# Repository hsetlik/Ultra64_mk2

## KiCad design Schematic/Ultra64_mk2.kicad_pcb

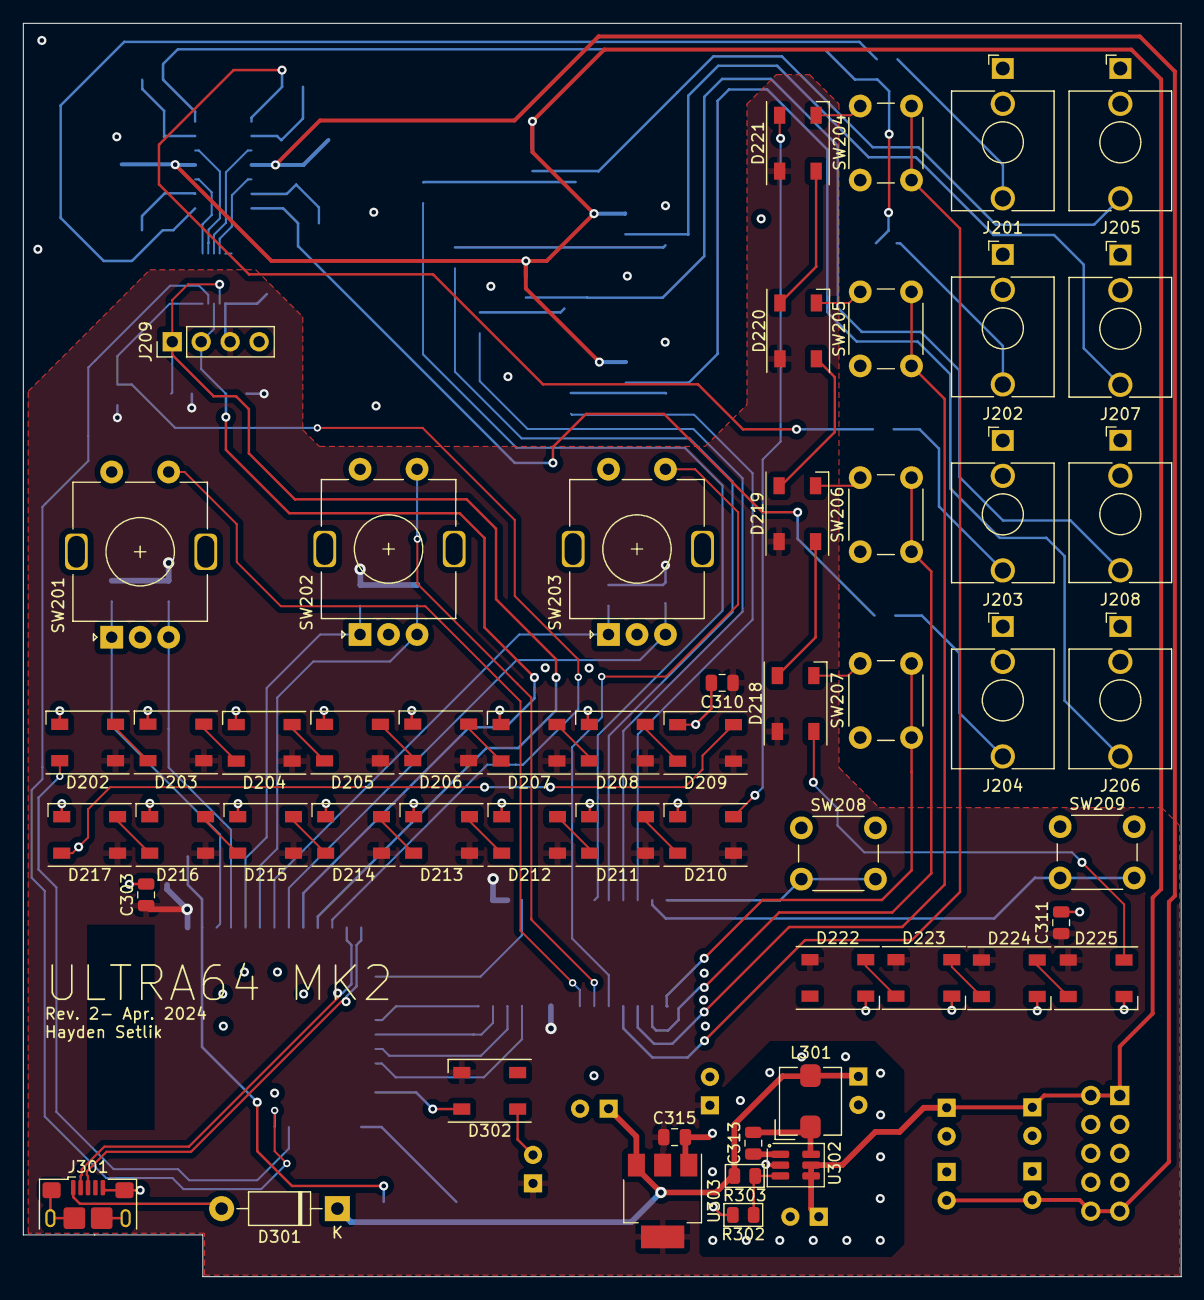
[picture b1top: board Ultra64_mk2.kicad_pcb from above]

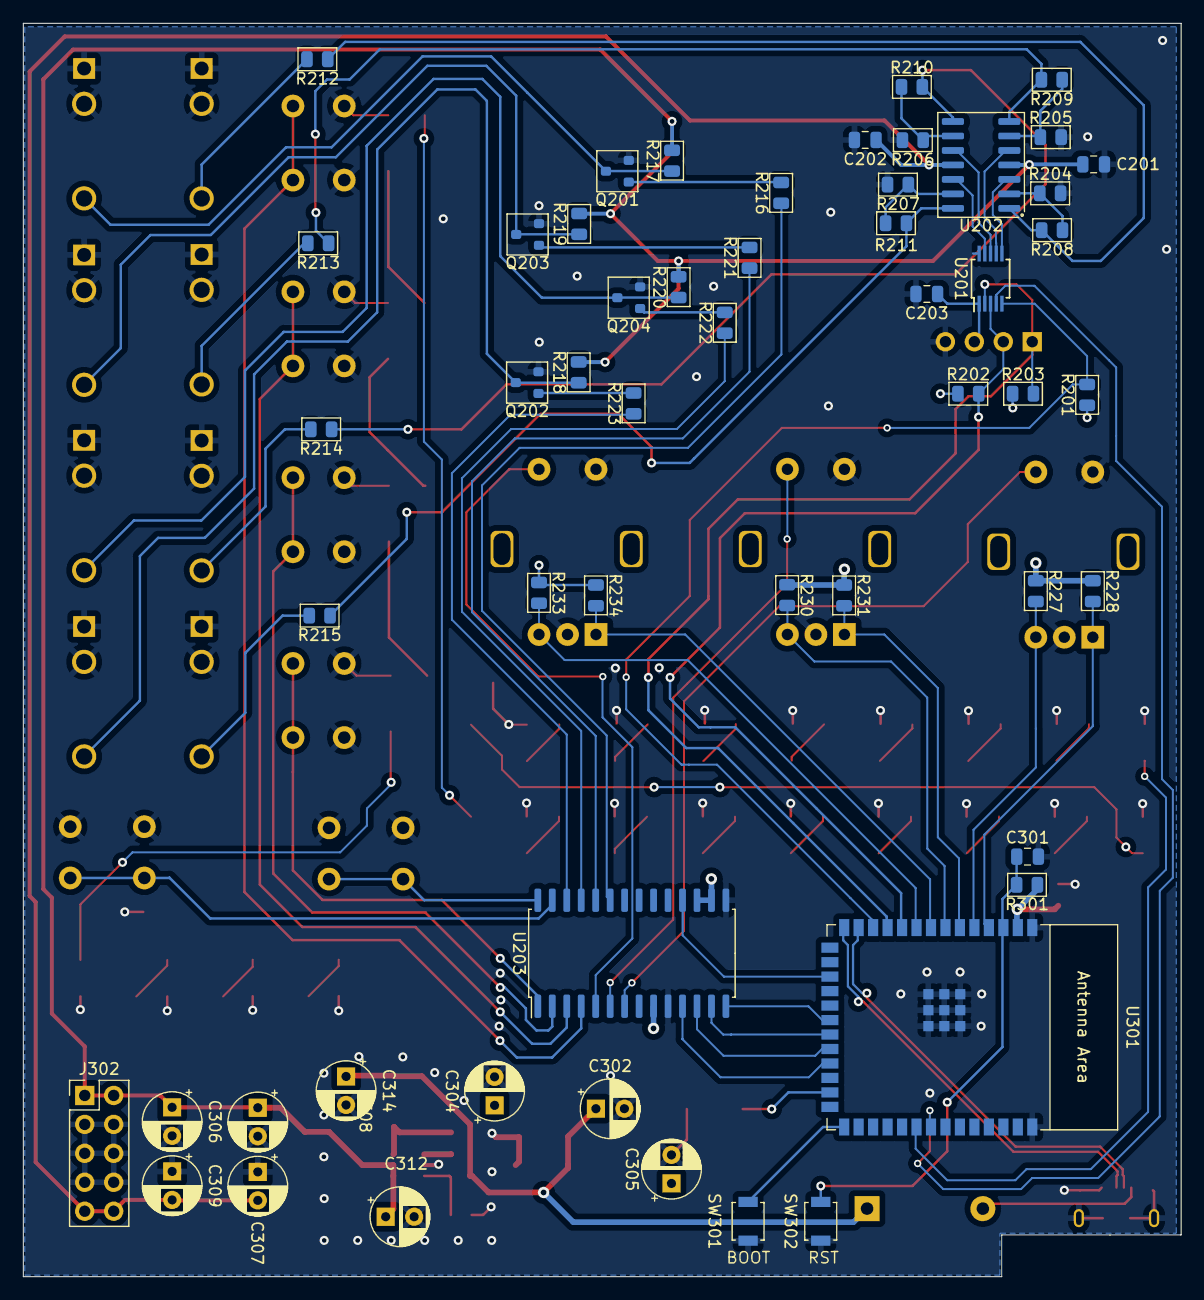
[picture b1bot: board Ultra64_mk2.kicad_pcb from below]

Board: 4 copper layers, 101.6 x 110.0 mm, 109 parts (54 on the bottom side), 90 nets.

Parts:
C201, C202, C203, C301, C303, C313: 0.1uF; C_0805_2012Metric
C302, C304, C305, C312, C314: 10uF; CP_Radial_D5.0mm_P2.50mm
C306, C307, C309: 22uF; CP_Radial_D5.0mm_P2.50mm
C308: 2.2uF; CP_Radial_D5.0mm_P2.50mm
C310: 2.2nF; C_0805_2012Metric
C311: 220nF; C_0805_2012Metric
C315: 2.2uF; C_0805_2012Metric
D202, D203, D204, D205, D206, D207, D208, D209, D210, D211, D212, D213, D214, D215, D216, D217, D218, D219, D220, D221, D222, D223, D224, D225: SK6812; LED_SK6812_PLCC4_5.0x5.0mm_P3.2mm
D301: 1N4002; D_DO-41_SOD81_P10.16mm_Horizontal
D302: WS2812B; LED_SK6812_PLCC4_5.0x5.0mm_P3.2mm
J201: CV1; Jack_3.5mm_QingPu_WQP-PJ398SM_Vertical_CircularHoles
J202: CV2; Jack_3.5mm_QingPu_WQP-PJ398SM_Vertical_CircularHoles
J203: CV3; Jack_3.5mm_QingPu_WQP-PJ398SM_Vertical_CircularHoles
J204: CV4; Jack_3.5mm_QingPu_WQP-PJ398SM_Vertical_CircularHoles
J205: GATE1; Jack_3.5mm_QingPu_WQP-PJ398SM_Vertical_CircularHoles
J206: GATE4; Jack_3.5mm_QingPu_WQP-PJ398SM_Vertical_CircularHoles
J207: GATE2; Jack_3.5mm_QingPu_WQP-PJ398SM_Vertical_CircularHoles
J208: GATE3; Jack_3.5mm_QingPu_WQP-PJ398SM_Vertical_CircularHoles
J209: Display; PinHeader_1x04_P2.54mm_Vertical
J301: USB_B_Micro; USB_Micro-B_Amphenol_10118193-0001LF_Horizontal
J302: Conn_02x05_Odd_Even; PinHeader_2x05_P2.54mm_Vertical
L301: 4.7uH; L_Bourns_SRP5030T
Q201, Q202, Q203, Q204: BC847; SOT-23
R201: 100k; R_0805_2012Metric
R202, R203: 2k2; R_0805_2012Metric
R204, R205, R206, R207: 47k; R_0805_2012Metric
R208, R209, R210, R211: 68k; R_0805_2012Metric
R212, R213, R214, R215: 220R; R_0805_2012Metric
R216, R221, R222, R223: 1k; R_0805_2012Metric
R217, R218, R219, R220, R227, R228, R230, R231, R233, R234, R301: 10k; R_0805_2012Metric
R302: 22k; R_0805_2012Metric
R303: 89k; R_0805_2012Metric
SW201, SW202, SW203: RotaryEncoder_Switch; RotaryEncoder_Alps_EC11E-Switch_Vertical_H20mm_5Pin
SW204, SW205, SW206, SW207, SW208, SW209: SW_SPST; SW_PUSH_6mm_H5mm
SW301, SW302: SW_SPST; SW_SPST_B3U-1000P
U201: MCP4728; MSOP-10_3x3mm_P0.5mm
U202: TL074; SOIC-14_3.9x8.7mm_P1.27mm
U203: MCP23S17_SO; SOIC-28W_7.5x17.9mm_P1.27mm
U301: ESP32-S3-WROOM-1
U302: LMR50410-Q; SOT-23-6_BigPads
U303: AMS1117; SOT-223-3_TabPin2

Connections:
+3.3V: C203.1, C303.1, C304.1, C305.1, C310.1, C311.1, C315.1, D202.3 (VDD), D203.3 (VDD), D204.3 (VDD), D205.3 (VDD), D206.3 (VDD), D207.3 (VDD), D208.3 (VDD), D209.3 (VDD), D210.3 (VDD), D211.3 (VDD), D212.3 (VDD), D213.3 (VDD), D214.3 (VDD), D215.3 (VDD), D216.3 (VDD), D217.3 (VDD), D218.3 (VDD), D219.3 (VDD), D220.3 (VDD), D221.3 (VDD), D222.3 (VDD), D223.3 (VDD), D224.3 (VDD), D225.3 (VDD), D302.1 (VDD), J209.3, R201.1, R202.1, R203.1, R227.1, R228.1, R230.1, R231.1, R233.1, R234.1, R301.1, U201.1 (VDD), U203.9 (VDD), U203.16 (A1), U203.17 (A2), U301.2 (3V3), U303.2 (VO)
+5V: C302.1, C314.1, D301.1 (K), L301.2, R303.2, U303.3 (VI)
+12V: C201.1, C306.1, C308.1, C312.1, J302.1, J302.2, R217.2, R218.2, R219.2, R220.2, U202.4 (V+), U302.4 (EN), U302.5 (VIN)
-12V: C202.1, C307.2, C309.2, J302.9, J302.10, U202.11 (V-)
C1: SW204.2 (B), U203.4 (GPB3)
C1_CV: J201.T, R212.2
C1_GATE: J205.T, Q201.3 (C), R217.1
C2: SW205.2 (B), U203.3 (GPB2)
C2_CV: J202.T, R213.2
C2_GATE: J207.T, Q203.3 (C), R219.1
C3: SW206.2 (B), U203.2 (GPB1)
C3_CV: J203.T, R214.2
C3_GATE: J208.T, Q204.3 (C), R220.1
C4: SW207.2 (B), U203.1 (GPB0)
C4_CV: J204.T, R215.2
C4_GATE: J206.T, Q202.3 (C), R218.1
DAC_RDY: R201.2, U201.5 (RDY/~BSY), U301.12 (GPIO8/TOUCH8/ADC1_CH7/SUBSPICS1)
EN: C301.1, R301.2, SW302.1 (A), U301.3 (EN)
ENCA_B: SW201.S1, U203.7 (GPB6)
ENCA_L: R228.2, SW201.A, U301.4 (GPIO4/TOUCH4/ADC1_CH3)
ENCA_R: R227.2, SW201.B, U301.5 (GPIO5/TOUCH5/ADC1_CH4)
ENCB_B: SW202.S1, U203.6 (GPB5)
ENCB_L: R231.2, SW202.A, U301.6 (GPIO6/TOUCH6/ADC1_CH5)
ENCB_R: R230.2, SW202.B, U301.7 (GPIO7/TOUCH7/ADC1_CH6)
ENCC_B: SW203.S1, U203.5 (GPB4)
ENCC_L: R234.2, SW203.A, U301.8 (GPIO15/U0RTS/ADC2_CH4/XTAL_32K_P)
ENCC_R: R233.2, SW203.B, U301.9 (GPIO16/U0CTS/ADC2_CH5/XTAL_32K_N)
EXP_CS: U203.11 (~CS), U301.23 (GPIO21)
EXP_RST: U203.18 (~RESET), U301.17 (GPIO9/TOUCH9/ADC1_CH8/FSPIHD/SUBSPIHD)
GND: C201.2, C202.2, C203.2, C301.2, C302.2, C303.2, C304.2, C305.2, C306.2, C307.1, C308.2, C309.1, C310.2, C311.2, C312.2, C314.2, C315.2, D202.1 (VSS), D203.1 (VSS), D204.1 (VSS), D205.1 (VSS), D206.1 (VSS), D207.1 (VSS), D208.1 (VSS), D209.1 (VSS), D210.1 (VSS), D211.1 (VSS), D212.1 (VSS), D213.1 (VSS), D214.1 (VSS), D215.1 (VSS), D216.1 (VSS), D217.1 (VSS), D218.1 (VSS), D219.1 (VSS), D220.1 (VSS), D221.1 (VSS), D222.1 (VSS), D223.1 (VSS), D224.1 (VSS), D225.1 (VSS), D302.3 (VSS), J201.S, J201.TN, J202.S, J202.TN, J203.S, J203.TN, J204.S, J204.TN, J205.S, J205.TN, J206.S, J206.TN, J207.S, J207.TN, J208.S, J208.TN, J209.4, J301.5 (GND), J301.6 (Shield), J302.3, J302.4, J302.5, J302.6, J302.7, J302.8, Q201.2 (E), Q202.2 (E), Q203.2 (E), Q204.2 (E), R204.2, R205.2, R206.2, R207.2, R302.2, SW201.C, SW201.S2, SW202.C, SW202.S2, SW203.C, SW203.S2, SW204.1 (A), SW205.1 (A), SW206.1 (A), SW207.1 (A), SW208.1 (A), SW209.1 (A), SW301.2 (B), SW302.2 (B), U201.10 (VSS), U203.10 (VSS), U203.15 (A0), U301.1 (GND), U301.40 (GND), U301.41 (GND), U302.2 (GND), U303.1 (ADJ)
LDAC: U201.4 (~LDAC), U301.33 (MTDO/GPIO40/CLK_OUT2)
MISO: U203.14 (SO), U301.20 (GPIO12/TOUCH12/ADC2_CH1/FSPICLK/FSPIIO6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)
MOSI: U203.13 (SI), U301.21 (GPIO13/TOUCH13/ADC2_CH2/FSPIQ/FSPIIO7/S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)
unnamed: D202.4 (DOUT), D203.2 (DIN)
unnamed: D203.4 (DOUT), D204.2 (DIN)
unnamed: D204.4 (DOUT), D205.2 (DIN)
unnamed: D205.4 (DOUT), D206.2 (DIN)
unnamed: D206.4 (DOUT), D207.2 (DIN)
unnamed: D207.4 (DOUT), D208.2 (DIN)
unnamed: D208.4 (DOUT), D209.2 (DIN)
unnamed: D209.4 (DOUT), D217.2 (DIN)
unnamed: D210.2 (DIN), D211.4 (DOUT)
unnamed: D210.4 (DOUT), D221.2 (DIN)
unnamed: D211.2 (DIN), D212.4 (DOUT)
unnamed: D212.2 (DIN), D213.4 (DOUT)
unnamed: D213.2 (DIN), D214.4 (DOUT)
unnamed: D214.2 (DIN), D215.4 (DOUT)
unnamed: D215.2 (DIN), D216.4 (DOUT)
unnamed: D216.2 (DIN), D217.4 (DOUT)
unnamed: D218.2 (DIN), D219.4 (DOUT)
unnamed: D218.4 (DOUT), D225.2 (DIN)
unnamed: D219.2 (DIN), D220.4 (DOUT)
unnamed: D220.2 (DIN), D221.4 (DOUT)
unnamed: D222.2 (DIN), D223.4 (DOUT)
unnamed: D223.2 (DIN), D224.4 (DOUT)
unnamed: D224.2 (DIN), D225.4 (DOUT)
unnamed: D302.2 (DOUT), U301.25 (GPIO48/SPICLK_N/SUBSPICLK_N_DIFF)
unnamed: Q201.1 (B), R216.2
unnamed: Q202.1 (B), R223.2
unnamed: Q203.1 (B), R221.2
unnamed: Q204.1 (B), R222.2
unnamed: R208.2, R212.1, U202.1
unnamed: R209.2, R213.1, U202.7
unnamed: R210.2, R214.1, U202.8
unnamed: R211.2, R215.1, U202.14
unnamed: SW301.1 (A), U301.27 (GPIO0/BOOT)
unnamed: U201.6 (VOUTA), U202.3 (+)
unnamed: U201.7 (VOUTB), U202.5 (+)
unnamed: U201.8 (VOUTC), U202.10 (+)
unnamed: U201.9 (VOUTD), U202.12 (+)
unnamed: R204.1, R208.1, U202.2 (-)
unnamed: R205.1, R209.1, U202.6 (-)
unnamed: R206.1, R210.1, U202.9 (-)
unnamed: R207.1, R211.1, U202.13 (-)
unnamed: R216.1, U203.23 (GPA2)
unnamed: R221.1, U203.24 (GPA3)
unnamed: R222.1, U203.25 (GPA4)
unnamed: R223.1, U203.26 (GPA5)
unnamed: C313.1, U302.1 (CB)
unnamed: R302.1, R303.1, U302.3 (FB)
unnamed: C313.2, L301.1, U302.6 (SW)
PG_LEFT: SW208.2 (B), U203.28 (GPA7)
PG_RIGHT: SW209.2 (B), U203.27 (GPA6)
PIXELS: D202.2 (DIN), U301.32 (MTCK/GPIO39/CLK_OUT3/SUBSPICS1)
SCK: U203.12 (SCK), U301.22 (GPIO14/TOUCH14/ADC2_CH3/FSPIWP/FSPIDQS/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)
SCL: J209.2, R202.2, U201.3 (SDA), U301.10 (GPIO17/U1TXD/ADC2_CH6)
SDA: J209.1, R203.2, U201.2 (SCL), U301.11 (GPIO18/U1RXD/ADC2_CH7/CLK_OUT3)
USB+: J301.3 (D+), U301.14 (GPIO20/U1CTS/ADC2_CH9/CLK_OUT1/USB_D+)
USB-: J301.2 (D-), U301.13 (GPIO19/U1RTS/ADC2_CH8/CLK_OUT2/USB_D-)
V_USB: D301.2 (A), J301.1 (VBUS)

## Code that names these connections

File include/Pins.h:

#pragma once
#include <Arduino.h>

// SPI
#define SCK 14
#define MOSI 13
#define MISO 12
#define EXP_CS 21
#define EXP_RST 9
#define HW_ADDR 0b110

// I2C
#define SDA 18
#define SCL 17
#define LDAC 8

// Pixels
#define PIXEL_PIN 39

// Rotary Encoders
#define ENCA_L 4
#define ENCA_R 5

#define ENCB_L 41
#define ENCB_R 40

#define ENCC_L 6
#define ENCC_R 39

//==========================================================
// MCP23S17 I/O Expander pins

#define CH1 2
#define CH2 3
#define CH3 4
#define CH4 5
#define P_LEFT 6
#define P_RIGHT 7

#define GATE1 8
#define GATE2 9
#define GATE3 10
#define GATE4 11
#define ENCA_B 12
#define ENCB_B 13
#define ENCC_B 14

// port A bit indeces

#define CH1_BIT 2
#define CH2_BIT 3
#define CH3_BIT 4
#define CH4_BIT 5
#define P_LEFT_BIT 6
#define P_RIGHT_BIT 7

// port B bit indeces

#define GATE1_BIT 0
#define GATE2_BIT 1
#define GATE3_BIT 2
#define GATE4_BIT 3
#define ENCC_BIT 4
#define ENCB_BIT 5
#define ENCA_BIT 6

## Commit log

2024-03-29 wiring up control stuff
2024-03-29 SPI and button handling
2024-03-29 Sequence state and controls
2024-03-29 timing and gate outputs
2024-03-30 message log and display stuff
2024-03-30 switched to FastLED, color math
2024-04-02 ISR safety stuff
2024-04-02 new ISR stuff
2024-04-02 Encoding output state in 64 bits
2024-04-07 Input ISR, pixel stuff
2024-04-07 Output ISR
2024-04-10 Rev. 2 schematic and PCB
2024-04-10 PCB in git
2024-05-18 fixed pins
2024-05-18 input ISR fixes
2024-05-18 new button class
2024-05-18 MCPButton banished
